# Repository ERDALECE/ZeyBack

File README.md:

# ZeyBack R2RDAC

High-performance DIY USB Audio / FPGA based R-2R DAC platform.

The STM32H750 MCU plays audio in 44.1 kHz - 768 kHz PCM and DSD64 - DSD512 DSD (DoP) formats. 

Optionally, a second USB audio input can be added by connecting an XMOS or AMANERO.

SPDIF audio input up to 192 kHz is possible via the CS8416 or directly through the FPGA input.

It has one coaxial and two optical inputs.

HDMI audio input is possible with the ADV7611.

Direct I2S signal pins are also provided. An external I2S signal can also be supplied as an input through these pins.

With the SI5340, the reclocking operation is performed within the FPGA.

Input selection via infrared remote control is possible using the RC5 code. Debugging can be done via a separate USB COM port. 
Status information (sample rate, bitrate, selected input, etc.) is output as SPI from the FPGA.
MCUs, displays, etc., can be connected to SPI pins to display information via a GUI.

Main PCB is 6 Layer, DSD PCB is 4 Layer. 

All tests have been completed and no serious bugs have been found. However, it is open to improvement.

This repository contains:
- STM32H750 USB Audio Class 2.0 (UAC2) firmware (PCM + DSD related work)
- FPGA logic used for audio data path / clocking / I2S/DSD processing
- Hardware design files (KiCad schematics/PCB, BOM, Gerbers)

## Repository structure

- `Firmware/Stm32/`  
  STM32H750 project (STM32CubeIDE). Includes STM32Cube/HAL and middleware components.

- `Firmware/Fpga/`  
  FPGA project files (Vivado project + sources).

- `Hardware/`  
  KiCad project files, BOM/CSV, and manufacturing outputs (Gerbers).
  
- `Pictures/` 
  Some testing and pcb pictures.

## Build / Tools

- STM32: STM32CubeIDE (or gcc-arm + Make/CMake if you prefer)
- FPGA: Xilinx Vivado
- Hardware: KiCad

## DSD Native / Volumio notes

Goal: DSD Native playback on Linux (Volumio / Raspberry Pi) with proper USB descriptors and, if required,
a targeted `snd-usb-audio` quirk limited to this device (VID+PID).

## Licensing (IMPORTANT)

This repository is **multi-licensed**:

- **Firmware** (our original code): **GPL-3.0-or-later**
- **Hardware design files** (KiCad schematics/PCB): **CERN-OHL-S-2.0**
- **Documentation** (if/when added under `docs/`): **CC BY-SA 4.0**
- **Third-party components** (e.g., STM32Cube/HAL, middleware): keep their **original licenses**
  as stated in file headers and vendor license texts.

See:
- `LICENSE` (GPLv3 for the main project codebase)
- `Firmware/LICENSE` (firmware scope)
- `Hardware/LICENSE` (hardware scope)
- `THIRD_PARTY_NOTICES.md`

## Status

Work in progress....
Hardware design files in this directory (KiCad schematics/PCB and related design sources)
are licensed under CERN-OHL-S-2.0 (Strongly Reciprocal).

Manufacturing outputs (Gerbers) are provided for convenience.

See THIRD_PARTY_NOTICES.md for any third-party footprints/symbols (if applicable).

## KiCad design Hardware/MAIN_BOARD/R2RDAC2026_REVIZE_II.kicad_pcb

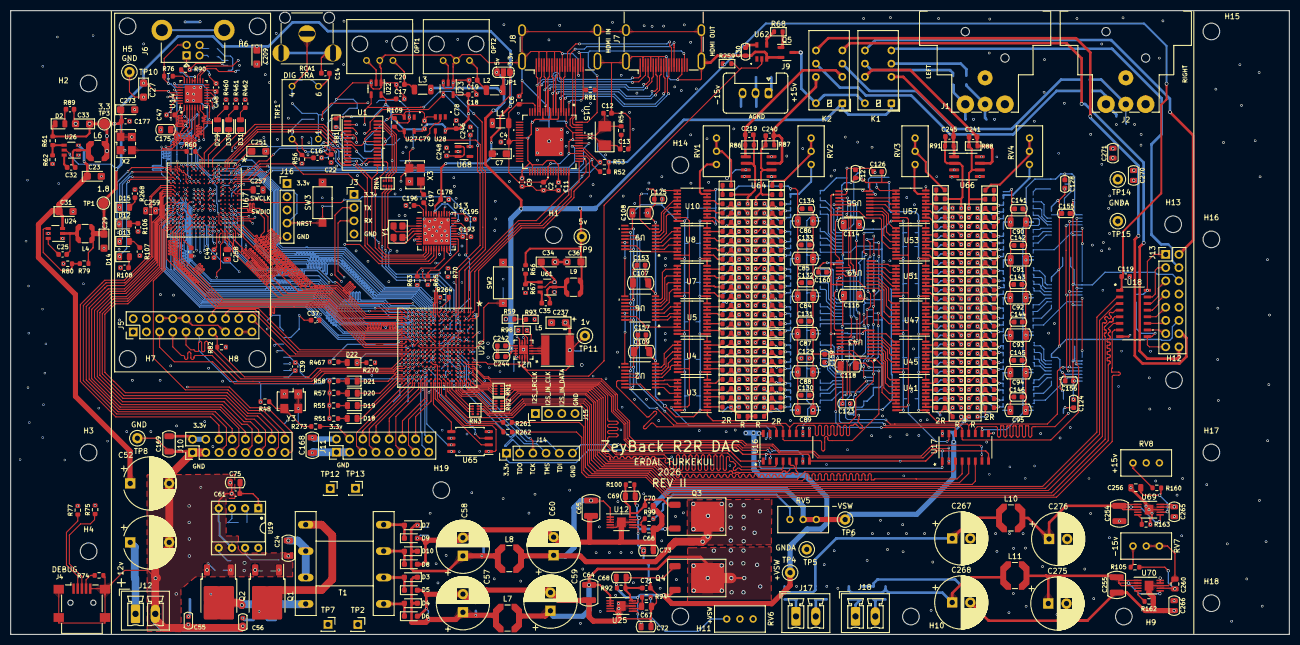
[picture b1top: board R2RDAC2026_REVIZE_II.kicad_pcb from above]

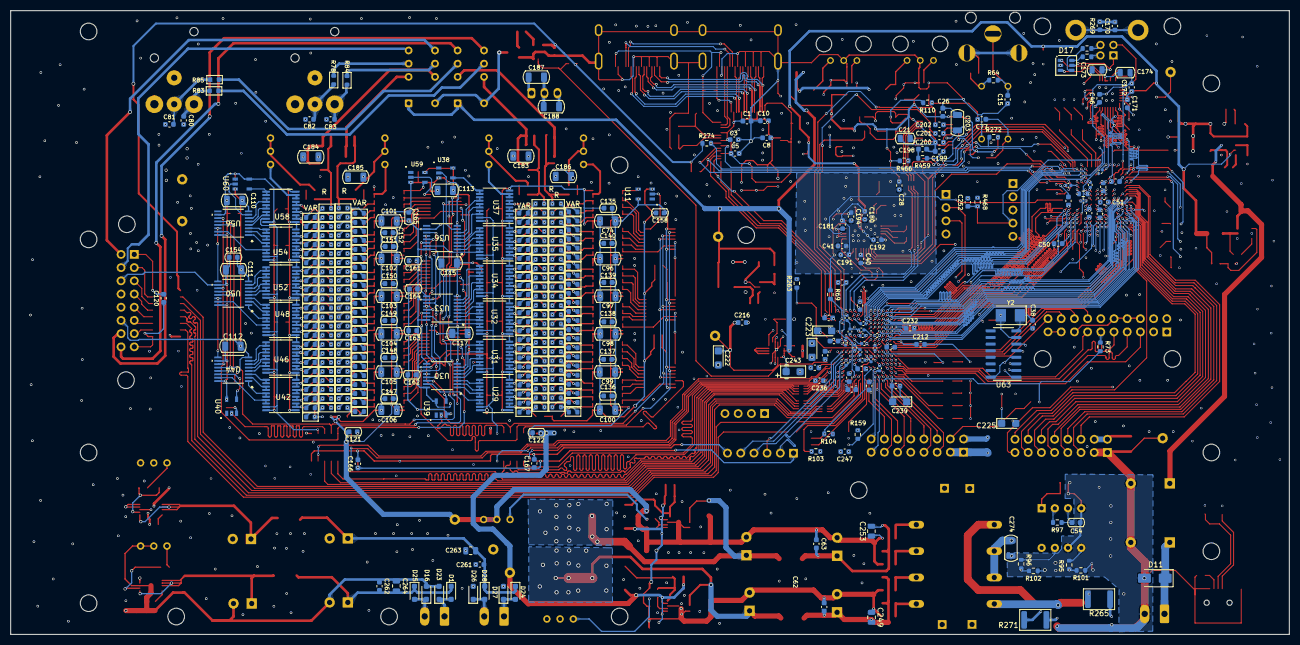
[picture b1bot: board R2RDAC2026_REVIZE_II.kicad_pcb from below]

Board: 6 copper layers, 246.0 x 120.0 mm, 940 parts (390 on the bottom side), 793 nets.

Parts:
C1, C2, C3, C4, C5, C6, C8, C9, C10, C11, C14, C15, C17, C18, C22, C26, C28, C30, C40, C41, C42, C43, C44, C46, C47, C48, C49, C50, C51, C78, C79, C119, C120, C121, C122, C123, C124, C125, C127, C128, C129, C130, C131, C132, C133, C134, C135, C136, C137, C139, C140, C141, C142, C143, C144, C145, C146, C147, C148, C149, C151, C152, C153, C154, C155, C156, C157, C158, C159, C160, C162, C163, C164, C165, C166, C167, C171, C172, C176, C177, C178, C180, C181, C191, C192, C193, C194, C195, C196, C197, C206, C221, C244, C250, C252: 100nf; C_0603_1608Metric
C7, C23, C27, C29, C33, C36, C209, C222, C223, C224, C225, C239, C251, C273: 10uf/6.3; CP_EIA-3216-18_Kemet-A
C12, C13: 22pf; C_0603_1608Metric
C16, C55, C56, C77: 10nf; C_0603_1608Metric
C19, C20: 1 uf; C_0603_1608Metric
C21: 1uf; C_0805_2012Metric
C24, C274: 10uF; C_1206_3216Metric
C25, C32, C35, C61, C62, C63, C179, C207, C212, C216, C226, C227, C229, C230, C231, C232, C233, C234, C235, C236, C238, C247, C261, C262: 100 nf; C_0603_1608Metric
C31, C34: 10uf/16v; CP_EIA-3216-18_Kemet-A
C37, C38: 22 pf; C_0603_1608Metric
C39, C200, C201, C202: 10 nf; C_0603_1608Metric
C45, C76, C189, C190, C204, C205, C208, C213, C214, C215, C217, C218, C220, C228, C272: 100 nf; C_0402_1005Metric
C52, C53: CP_Radial_D8.0mm_P2.50mm; CP_Radial_D10.0mm_P7.50mm
C54: 470pf; C_0603_1608Metric
C57, C58, C59, C60: 1000uf/10v; CP_Radial_D10.0mm_P3.50mm
C64, C65, C254, C255: 47uf/10v; C_1210_3225Metric
C66, C67, C256, C260: 4.7uf; C_0805_2012Metric
C68, C69, C72, C73, C265, C266, C270, C271: 10uf; C_0805_2012Metric
C70, C71, C246, C248: 4.7uf; C_0603_1608Metric
C74, C84, C85, C86, C87, C88, C89, C90, C91, C92, C93, C94, C95, C96, C97, C98, C99, C100, C101, C102, C103, C104, C105, C106, C107, C108, C109, C110, C111, C112, C113, C114, C115, C116, C117, C118, C168, C169, C183, C184, C185, C186, C187, C188, C203: 100uf; C_1206_3216Metric
C75: 10uF; C_0805_2012Metric
C80, C81, C82, C83, C219, C240, C241, C245: 100 pf; C_0603_1608Metric
C126, C138, C150, C161: 100uf; C_0603_1608Metric
C170, C199: 1 nf; C_0603_1608Metric
C173, C174, C175: 2.2uf; C_0805_2012Metric
C182, C210, C211, C269: 100nf; C_0402_1005Metric
C198: 22 nf; C_0603_1608Metric
C237: 47uf/6.3; CP_EIA-3216-18_Kemet-A
C242: 3.3nf; C_0603_1608Metric
C243: 4,7uF/16; CP_EIA-3216-18_Kemet-A
C249, C257, C258, C259, C263: 1 uf; C_0805_2012Metric
C253, C264: 1 uF; C_0805_2012Metric
C267, C268, C275, C276: 470uf/16v; CP_Radial_D10.0mm_P3.50mm
D1, D3, D4, D5, D6, D7, D8, D9, D10, D16, D23, D24, D25, D26, D27, D28: DSS20-0015B; D_SOD-323_HandSoldering
D2, D12, D13, D14, D15, D18, D19, D20, D21, D22, D29, D30, D31: RED; LED_0805_2012Metric
D11: DSS20-0015B; D_SMA
D17: USBLC6-2SC6; SOT-23-6
FB1: FerriteBead_Small; R_0603_1608Metric
H1, H2, H3, H4, H5, H6, H7, H8, H9, H10, H11, H12, H13, H14, H15, H16, H17, H18, H19: MountingHole; MountingHole_3.2mm_M3
J1, J2: NC3MBH-B; Jack_XLR_Neutrik_NC3MBH-B_Horizontal
J3: Conn_01x04; PinHeader_1x04_P2.54mm_Vertical
J4: USB_B_Micro; USB_Mini-B_Lumberg_2486_01_Horizontal
J5: XMOS; PinHeader_2x10_P2.54mm_Vertical
J6: USB_B; USB_B_Lumberg_2411_02_Horizontal
J7, J8: HDMI_A; HDMI_A_Molex_208658-1001_Horizontal
J9: Conn_01x03_Pin; Stocko_MKS_1653-6-0-303_1x3_P2.50mm_Vertical
J10, J11, J13: Conn_02x08_Odd_Even; PinHeader_2x08_P2.54mm_Vertical
J12, J17, J18: Conn_01x02; PhoenixContact_MCV_1,5_2-G-3.81_1x02_P3.81mm_Vertical
J14: Conn_01x06; PinHeader_1x06_P2.54mm_Vertical
J15: Conn_01x04_Pin; PinHeader_1x04_P2.54mm_Vertical
J16: Conn_01x05; PinHeader_1x05_P2.54mm_Vertical
JP1: Jumper_3_Open; SolderJumper-3_P1.3mm_Open_RoundedPad1.0x1.5mm_NumberLabels
K1, K2: EC2-5NU; Relay_DPDT_Kemet_EC2
L1: 10 uH; L_1206_3216Metric
L2, L3: 1 uH; L_1206_3216Metric
L4, L9: 2,2uH; L_Coilcraft_LPS3314
L5: 2.2uh; L_Taiyo-Yuden_NR-60xx
L6: 3,3uH; L_Coilcraft_LPS4018
L7, L8, L10, L11: 10uH; L_Coilcraft_LPS5030
OPT1, OPT2: TORX177
Q1, Q2: IRFR120N; TO-252-2
Q3, Q4: MJD44H11; TO-252-2
Q5: BC847; SOT-23-3
R1, R2, R3, R4, R5, R6, R7, R8, R16, R19, R21, R23, R25, R27, R29, R31, R33, R35, R37, R39, R41, R43, R45, R47, R49, R111, R112, R114, R116, R118, R120, R122, R124, R126, R128, R130, R132, R134, R136, R138, R140, R142, R144, R146, R148, R150, R152, R154, R156, R158, R164, R165, R166, R167, R170, R171, R174, R175, R178, R179, R182, R183, R186, R187, R190, R191, R194, R195, R198, R199, R202, R203, R206, R207, R210, R211, R214, R215, R218, R219, R222, R223, R226, R227, R230, R231, R234, R235, R238, R239, R242, R243, R246, R247, R250, R251, R254, R255, R258, R260: 2R; R_0603_1608Metric
R9, R10, R11, R12, R13, R14, R15, R17, R18, R20, R22, R24, R26, R28, R30, R32, R34, R36, R38, R40, R42, R44, R46, R113, R115, R117, R119, R121, R123, R125, R127, R129, R131, R133, R135, R137, R139, R141, R143, R145, R147, R149, R151, R153, R155, R157, R168, R169, R172, R173, R176, R177, R180, R181, R184, R185, R188, R189, R192, R193, R196, R197, R200, R201, R204, R205, R208, R209, R212, R213, R216, R217, R220, R221, R224, R225, R228, R229, R232, R233, R236, R237, R240, R241, R244, R245, R248, R249, R252, R253, R256, R257, R275, R276, R277, R278, R279, R280, R281, R282, R283, R284, R285, R286, R287, R288, R289, R290, R291, R292, R293, R294, R295, R296, R297, R298, R299, R300, R301, R302, R303, R304, R305, R306, R307, R308, R309, R310, R311, R312, R313, R314, R315, R316, R317, R318, R319, R320, R321, R322, R323, R324, R325, R326, R327, R328, R329, R330, R331, R332, R333, R334, R335, R336, R337, R338, R339, R340, R341, R342, R343, R344, R345, R346, R347, R348, R349, R350, R351, R352, R353, R354, R355, R356, R357, R358, R359, R360, R361, R362, R363, R364, R365, R366: R; R_0603_1608Metric
R48, R60, R73, R273: 33; R_0603_1608Metric
R50, R161, R266, R267, R367, R368, R369, R370, R371, R372, R373, R374, R375, R376, R377, R378, R379, R380, R381, R382, R383, R384, R385, R386, R387, R388, R389, R390, R391, R392, R393, R394, R395, R396, R397, R398, R399, R400, R401, R402, R403, R404, R405, R406, R407, R408, R409, R410, R411, R412, R413, R414, R415, R416, R417, R418, R419, R420, R421, R422, R423, R424, R425, R426, R427, R428, R429, R430, R431, R432, R433, R434, R435, R436, R437, R438, R439, R440, R441, R442, R443, R444, R445, R446, R447, R448, R449, R450, R451, R452, R453, R454, R455, R456, R457, R458: VAR; R_0603_1608Metric
R51, R55, R57, R58, R68, R162, R163, R263, R270, R467: 1k; R_0603_1608Metric
R52, R53, R81, R82, R272, R466: 4,7k; R_0603_1608Metric
R54: 390k; R_0603_1608Metric
R56, R64: 75; R_0603_1608Metric
R59: 51k; R_0603_1608Metric
R61: 22.1k; R_0603_1608Metric
R62, R98: 100k; R_0603_1608Metric
R63, R65, R69, R70, R71, R72, R261, R262: 22; R_0603_1608Metric
R66: 54.9k; R_0603_1608Metric
R67, R80, R90, R92, R100, R109, R259, R274, R468, R470: 10k; R_0603_1608Metric
R74: 1,5k; R_0603_1608Metric
R75, R77: 27; R_0603_1608Metric
R76: 8.06k; R_0603_1608Metric
R78, R83, R84, R85, R86, R87, R88, R91, R110: 100; R_0603_1608Metric
R79: 13,7k; R_0603_1608Metric
R89, R106, R107, R108, R268, R460, R461, R462: 1k; C_0603_1608Metric
R93: 200k; R_0603_1608Metric
R94, R99, R105, R160: 31k; R_0603_1608Metric
R95, R96: 10; R_0603_1608Metric
R97: 15k; R_0603_1608Metric
R101, R102: 47k; R_0603_1608Metric
R103, R104, R159, R264: 4.7k; R_0603_1608Metric
R265, R271: 10; R_1812_4532Metric
R269: 1m; C_0603_1608Metric
R459: 3k; R_0603_1608Metric
RCA1: RCA
RN1, RN2, RN3, RN4: R_4x0402_Convex; R_Array_Convex_4x0402
RV1, RV2, RV3, RV4: 50; Potentiometer_Bourns_3296W_Vertical
RV5, RV6, RV7, RV8: 2.2k; Potentiometer_Bourns_3296W_Vertical
SW2, SW3: SW_Push; SW_SPST_CK_RS282G05A3
T1: Transformer_1P_2S; EE2006
TP1, TP3: TestPoint; TestPoint_Pad_D2.0mm
TP2, TP7, TP12, TP13: TestPoint; PinSocket_1x01_P2.54mm_Vertical
TP4, TP5, TP6, TP8, TP9, TP10, TP14, TP15: TestPoint; TestPoint_Loop_D2.50mm_Drill1.0mm
TP11: 1v; TestPoint_Loop_D2.50mm_Drill1.0mm
TRF1: DIGITALTRAFO
U1: CS8416-xZZ; TSSOP-28_4.4x9.7mm_P0.65mm
U2, U6, U9, U30, U33, U36, U43, U44, U49, U50, U55, U56: 74LS595; TSSOP16_SOT403-1_NXP_NEX
U3, U4, U5, U7, U8, U10, U29, U31, U32, U34, U35, U37, U41, U42, U45, U46, U47, U48, U51, U52, U53, U54, U57, U58: SN74LVC245AN; TSSOP-20_4.4x6.5mm_P0.65mm
U11, U27, U28, U38, U39, U40, U59, U60, U62: SN74LVC1G04DBVR; SOT-753
U12, U25, U69, U70: LT3042xMSE; MSOP-10-1EP_3x3mm_P0.5mm_EP1.68x1.88mm
U13: Si5342A-D; QFN-44-1EP_7x7mm_P0.5mm_EP5.2x5.2mm
U14: USB3320C-EZK; QFN32_5X5MC_MCH
U15: ADV7611BSWZ; SW_64_2_ADI
U16, U17, U18: SI8660BC-B-IS1R; SOIC16_SI823_SKY
U19: IR2153; DIP-8_W7.62mm_Socket
U20: XC7A100T-CSG324; BGA-324_15.0x15.0mm_Layout18x18_P0.8mm_Ball0.45mm_Pad0.4mm_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
U21: TPS62130RGTT; TPS62130
U22, U23: SN74LVC1G125DBVR; SOT-23-5
U24, U26, U61: TPS562201DDCR; DDC0006A_N
U63: CH340G; SOIC-16_3.9x9.9mm_P1.27mm
U64, U66: OPA2134UA; SOIC-8_3.9x4.9mm_P1.27mm
U65: W25Q128JVS; SOIC-8_5.23x5.23mm_P1.27mm
U67: STM32H750XBHx; TFBGA-265_14x14mm_Layout17x17_P0.8mm
U68: AP2127K-1.8; SOT-23-5
X1: 28.63636 mhz; Crystal_SMD_5032-2Pin_5.0x3.2mm
X2, X3: 24.576 mhz; Oscillator_SMD_SeikoEpson_SG8002LB-4Pin_5.0x3.2mm
Y1: Crystal_GND24; Crystal_SMD_3225-4Pin_3.2x2.5mm
Y2: 12 Mhz; Crystal_SMD_5032-2Pin_5.0x3.2mm
Y3: 50mhz; Oscillator_SMD_EuroQuartz_XO53-4Pin_5.0x3.2mm_HandSoldering

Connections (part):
1.8V_ENB: R98.2, U21.4 (PG), U24.5 (EN)
1.8v ADV: C246.1, L1.1 (+), U68.5 (VOUT)
24Mhz_ULPI: U14.26 (REFCLK), U67.E15 (PA8)
+1V0: C76.1, C190.1, C205.1, C213.1, C214.1, C215.1, C216.1, C217.1, C218.1, C220.1, C222.1, C223.1, C237.1, L5.1 (+), R59.1, TP11.1, U20.F8 (VCCINT), U20.F10 (VCCBRAM), U20.G7 (VCCINT), U20.G9 (VCCINT), U20.G11 (VCCBRAM), U20.H8 (VCCINT), U20.J7 (VCCINT), U20.J11 (VCCINT), U20.K8 (VCCINT), U20.L7 (VCCINT), U20.L11 (VCCINT), U20.M8 (VCCINT), U20.M10 (VCCINT), U20.N7 (VCCINT), U20.N9 (VCCINT), U20.N11 (VCCINT), U21.14 (VOS)
+1V8: C27.1, C29.1, C45.1, C171.1, C172.1, C178.1, C179.1, C180.1, C181.1, C191.1, C204.1, C207.1, C208.1, C209.1, L4.2, R79.1, TP1.1, U13.21 (VDD), U13.32 (VDD), U13.39 (VDD), U13.40 (VDD), U14.28 (VDD18), U14.30 (VDD18), U20.E8 (VCCBATT_0), U20.F12 (VCCAUX), U20.H10 (VCCADC_0), U20.H12 (VCCAUX), U20.K12 (VCCAUX), U20.M12 (VCCAUX), U26.5 (EN)
+3.3V: C8.1, C9.1, C10.1, C11.1, C17.1, C18.1, C21.2, C22.2, C26.2, C28.1, C30.1, C33.1, C39.1, C40.1, C41.1, C42.1, C43.1, C44.1, C46.1, C47.1, C48.1, C49.1, C50.1, C51.1, C78.1, C79.1, C119.1, C166.1, C167.1, C168.1, C169.1, C174.1, C175.2, C176.1, C177.1, C182.1, C189.1, C192.1, C193.1, C194.1, C195.1, C206.1, C210.1, C211.1, C212.1, C221.1, C224.1, C225.1, C226.1, C227.1, C228.1, C229.1, C230.1, C231.1, C232.1, C233.1, C234.1, C235.1, C236.1, C238.1, C239.1, C247.1, C248.1, C250.1, C251.1, C269.1, C272.1, C273.1, D2.1, FB1.1, J3.1, J10.2, J10.4, J11.2, J14.1, J16.1, JP1.3 (B), L6.2, R52.1, R53.2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
+3.3VP: J5.17, J5.19
+5V: C36.1, C243.1, C244.1, JP1.1 (A), K1.1, K2.1, L9.2, R66.1, R98.1, TP9.1, U21.10 (AVIN), U21.11 (PVIN), U21.12 (PVIN), U21.13 (EN)
+12V: C23.1, C24.1, C31.1, C34.1, C52.1, C53.1, C61.2, C75.2, C274.1, D11.1 (K), J12.1, T1.2, T1.3, U19.1 (VCC), U19.8 (VB), U24.3 (VIN), U26.3 (VIN), U61.3 (VIN), U61.5 (EN)
+15V: C183.1, C184.1, C187.1, C265.1, C270.1, J9.1, U64.8 (V+), U66.8 (V+), U69.9 (OUTS), U69.10 (OUT)
+VSW: C68.2, C72.1, C74.1, C84.1, C85.1, C86.1, C87.1, C88.1, C89.1, C90.1, C91.1, C92.1, C93.1, C94.1, C95.1, C96.1, C97.1, C98.1, C99.1, C100.1, C101.1, C102.1, C103.1, C104.1, C105.1, C106.1, C107.1, C108.1, C109.1, C110.1, C111.1, C112.1, C113.1, C114.1, C115.1, C116.1, C117.1, C118.1, C121.1, C122.1, C123.1, C124.1, C125.1, C126.1, C127.1, C128.1, C129.1, C130.1, C131.1, C132.1, C133.1, C134.1, C135.1, C136.1, C137.1, C138.1, C139.1, C140.1, C141.1, C142.1, C143.1, C144.1, C145.1, C146.1, C147.1, C148.1, C149.1, C150.1, C151.1, C152.1, C153.1, C154.1, C155.1, C156.1, C157.1, C158.1, C159.1, C160.1, C161.1, C162.1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
-15V: C185.1, C186.1, C188.1, C255.1, C260.2, C262.1, C264.1, C266.2, C268.2, C271.1, C275.2, D16.2 (A), D23.2 (A), J9.3, R162.1, RV7.1, RV7.2, U64.4 (V-), U66.4 (V-), U70.8 (GND), U70.11 (GND)
-VSW: C58.2, C60.2, C63.1, C65.1, C66.2, C70.2, C73.2, C74.2, C84.2, C85.2, C86.2, C87.2, C88.2, C89.2, C90.2, C91.2, C92.2, C93.2, C94.2, C95.2, C96.2, C97.2, C98.2, C99.2, C100.2, C101.2, C102.2, C103.2, C104.2, C105.2, C106.2, C107.2, C108.2, C109.2, C110.2, C111.2, C112.2, C113.2, C114.2, C115.2, C116.2, C117.2, C118.2, C121.2, C122.2, C123.2, C124.2, C125.2, C126.2, C127.2, C128.2, C129.2, C130.2, C131.2, C132.2, C133.2, C134.2, C135.2, C136.2, C137.2, C138.2, C139.2, C140.2, C141.2, C142.2, C143.2, C144.2, C145.2, C146.2, C147.2, C148.2, C149.2, C150.2, C151.2, C152.2, C153.2, C154.2, C155.2, C156.2, C157.2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
A0: U20.M2 (IO_L4N_T0_34), U67.G4 (PF0)
A1: U20.K3 (IO_L2P_T0_34), U67.G3 (PF1)
BCLK_L: U2.11 (SRCLK), U6.11 (SRCLK), U9.11 (SRCLK), U16.13 (B3), U30.11 (SRCLK), U33.11 (SRCLK), U36.11 (SRCLK)
BCLK_L_F: RN1.3 (R3.1), U16.4 (A3)
BCLK_R: U17.13 (B3), U43.11 (SRCLK), U44.11 (SRCLK), U49.11 (SRCLK), U50.11 (SRCLK), U55.11 (SRCLK), U56.11 (SRCLK)
BCLK_R_F: RN2.3 (R3.1), U17.4 (A3)
CCLK: U20.E9 (CCLK_0), U65.6 (CLK)
CEC: J7.13 (CEC), J8.13 (CEC)
COAX: C16.2, U1.4 (RXP0)
COAX_FPGA_IN: C77.2, R110.1
COAX_FPGA_OUT: U20.E2 (IO_L14P_T2_SRCC_35), U28.4 (Y)
CSB: U1.14 (AD0/~CS/NV/RERR), U67.D2 (PE4)
CSB_SI: U13.16 (A0/~CS), U67.A3 (PI5)
CSO: R103.2, U20.L13 (IO_L6P_T0_FCS_B_14), U65.1 (~CS)
D0: U20.K17 (IO_L1P_T0_D00_MOSI_14), U65.5 (DI(IO0))
D1: U20.K18 (IO_L1N_T0_D01_DIN_14), U65.2 (DO(IO1))
D2: R104.2, U20.L14 (IO_L2P_T0_D02_14), U65.3 (IO2)
D3: R159.2, U20.M14 (IO_L2N_T0_D03_14), U65.7 (IO3)
D+: D17.3 (L2), U14.18 (DP)
D-: D17.1 (L1), U14.19 (DM)
DATA_N_L: U16.11 (B5), U39.2 (A)
DATA_N_L_F: RN1.1 (R1.1), U16.6 (A5)
DATA_N_R: U17.11 (B5), U40.2 (A)
DATA_N_R_F: RN2.1 (R1.1), U17.6 (A5)
DATA_P_L: U2.14 (SER), U16.14 (B2)
DATA_P_L_F: RN1.4 (R4.1), U16.3 (A2)
DATA_P_R: U17.14 (B2), U43.14 (SER)
DATA_P_R_F: RN2.4 (R4.1), U17.3 (A2)
DIR: U14.31 (DIR), U67.F4 (PI11)
DS0: U20.U7 (IO_L22P_T3_34), U67.P16 (PD14)
DS1: U20.P3 (IO_L14N_T2_SRCC_34), U67.P15 (PD15)
DS2: U20.R5 (IO_L19N_T3_VREF_34), U67.D13 (PD0)
DS3: U20.N2 (IO_L3P_T0_DQS_34), U67.E12 (PD1)
DS4: U20.R2 (IO_L15N_T2_DQS_34), U67.U9 (PE7)
DS5: U20.P2 (IO_L15P_T2_DQS_34), U67.T9 (PE8)
DS6: U20.T1 (IO_L17N_T2_34), U67.P9 (PE9)
DS7: U20.R1 (IO_L17P_T2_34), U67.N9 (PE10)
DS8: U20.U1 (IO_L7P_T1_34), U67.P10 (PE11)
DS9: U20.V1 (IO_L7N_T1_34), U67.R10 (PE12)
DS10: U20.R7 (IO_L23P_T3_34), U67.T10 (PE13)
DS11: U20.R8 (IO_L24P_T3_34), U67.U10 (PE14)
DS12: U20.T3 (IO_L11N_T1_SRCC_34), U67.R11 (PE15)
DS13: U20.U9 (IO_L21P_T3_DQS_34), U67.U16 (PD8)
DS14: U20.U8 (IO_25_34), U67.T17 (PD9)
DS15: U20.V9 (IO_L21N_T3_DQS_34), U67.T16 (PD10)
DS16: U20.N6 (IO_L18N_T2_34), U67.T13 (PH8)
DS17: U20.R6 (IO_L19P_T3_34), U67.R13 (PH9)
DS18: U20.P4 (IO_L14P_T2_SRCC_34), U67.P13 (PH10)
DS19: U20.R3 (IO_L11P_T1_SRCC_34), U67.P14 (PH11)
DS20: U20.T6 (IO_L23N_T3_34), U67.R14 (PH12)
DS21: U20.V6 (IO_L20N_T3_34), U67.D16 (PH13)
DS22: U20.U6 (IO_L22N_T3_34), U67.B17 (PH14)
DS23: U20.V5 (IO_L10P_T1_34), U67.B16 (PH15)
DS24: U20.V4 (IO_L10N_T1_34), U67.A16 (PI0)
DS25: U20.U3 (IO_L8N_T1_34), U67.A15 (PI1)
DS26: U20.U4 (IO_L8P_T1_34), U67.B15 (PI2)
DS27: U20.N4 (IO_L16N_T2_34), U67.C14 (PI3)
DS28: U20.M6 (IO_L18P_T2_34), U67.A2 (PI6)
DS29: U20.L3 (IO_L2N_T0_34), U67.B3 (PI7)
DS30: U20.L4 (IO_L5N_T0_34), U67.E2 (PI9)
DS31: U20.L1 (IO_L1P_T0_34), U67.F3 (PI10)
DSD_A: RN3.3 (R3.1), U18.3 (A2)
DSD_A_N: R261.2, U18.6 (A5)
DSD_B: RN3.2 (R2.1), U18.4 (A3)
DSD_B_N: R262.2, U18.7 (A6)
DSD_CLK: RN3.4 (R4.1), U18.2 (A1)
DSD_EN: U18.5 (A4), U20.H17 (IO_L18P_T2_A24_15)
DSD_EN_RL: R259.1, U20.A13 (IO_L9P_T1_DQS_AD3P_15), U62.2 (A)
DSD_ON: J5.13, R82.2, U20.V12 (IO_L20N_T3_A07_D23_14)
F0: J5.14, U20.V10 (IO_L21P_T3_DQS_14)
F1: J5.16, U20.T10 (IO_L24N_T3_A00_D16_14)
F2: J5.18, U20.V11 (IO_L21N_T3_DQS_A06_D22_14)
F3: J5.20, U20.U11 (IO_L19N_T3_A09_D25_VREF_14)
GND: C1.2, C2.2, C3.2, C4.2, C5.2, C6.2, C7.2, C8.2, C9.2, C10.2, C11.2, C12.2, C13.2, C15.1, C17.2, C18.2, C19.1, C20.1, C21.1, C22.1, C23.2, C24.2, C26.1, C27.2, C28.2, C29.2, C30.2, C31.2, C33.2, C34.2, C36.2, C37.1, C38.2, C39.2, C40.2, C41.2, C42.2, C43.2, C44.2, C45.2, C46.2, C47.2, C48.2, C49.2, C50.2, C51.2, C52.2, C53.2, C54.2, C55.2, C56.2, C61.1, C75.1, C76.2, C78.2, C79.2, C119.2, C166.2, C167.2, C168.2, C169.2, C170.2, C171.2, C172.2, C173.2, C174.2, C175.1, C176.2, C177.2, C178.2, C179.2, C180.2, C181.2, C182.2, C189.2, C190.2, C191.2, C192.2, C193.2, C194.2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
GNDA: C57.2, C59.2, C62.1, C64.1, C67.2, C69.2, C71.2, C72.2, C73.1, C80.2, C81.1, C82.1, C83.2, C183.2, C184.2, C185.2, C186.2, C187.2, C188.2, C249.1, C254.1, C256.2, C261.1, C263.1, C265.2, C266.1, C267.2, C270.2, C271.2, C276.2, D5.2 (A), D6.2 (A), D26.2 (A), D27.2 (A), J1.1, J1.G, J2.1, J2.G, J9.2, J13.10, Q3.3 (E), R100.1, R163.1, RV6.1, RV6.2, RV8.1, RV8.2, TP5.1, TP14.1, TP15.1, U12.6 (PGFB), U12.9 (OUTS), U25.5 (ILIM), U25.8 (GND), U25.11 (GND), U64.3 (+), U64.5 (+), U66.3 (+), U66.5 (+), U69.8 (GND), U69.11 (GND), U70.9 (OUTS), U70.10 (OUT)
HDMI_I2S_BCLK: U15.49 (SCLK/INT2), U20.A1 (IO_L9N_T1_DQS_AD7N_35)
HDMI_I2S_DATA: U15.48 (AP), U20.B2 (IO_L10N_T1_AD15N_35)
HDMI_I2S_LRCLK: U15.50 (LRCLK), U20.B1 (IO_L9P_T1_DQS_AD7P_35)
HDMI_INDSCL: J8.15 (SCL), U15.62 (DDCA_SCL)
HDMI_INDSDA: J8.16 (SDA), U15.63 (DDCA_SDA)
HDMI_IN_5v: J7.18 (+5V), J8.18 (+5V), R81.1, U15.64 (RXA_5V)
HDMI_IN_INT1: U15.55 (INT1), U67.B4 (PE1)
HDMI_IN_MCLK: U15.51 (MCLK/INT2), U20.B3 (IO_L10P_T1_AD15P_35)
HDMI_IN_RESET: R274.2, U15.56 (*RESET), U67.A4 (PI4)
HDMI_IN_SCL: R52.2, U15.53 (SCL), U67.B5 (PB6)
HDMI_IN_SDA: R53.1, U15.54 (SDA), U67.C5 (PB7)
HPD: J8.19 (HPD), R81.2, U15.1 (HPA_A/INT2)
I2S_IN_CLK: J15.2, U20.D15 (IO_L12P_T1_MRCC_15)
I2S_IN_DATA: J15.3, U20.E16 (IO_L11N_T1_SRCC_15)
I2S_IN_LRCLK: J15.1, U20.E15 (IO_L11P_T1_SRCC_15)
IO0: J11.5, U20.U18 (IO_L17N_T2_A13_D29_14)
IO1: J11.6, U20.T18 (IO_L7N_T1_D10_14)
IO2: J11.7, U20.R17 (IO_L12N_T1_MRCC_14)
IO3: J11.8, U20.R18 (IO_L7P_T1_D09_14)
IO4: J11.9, U20.R16 (IO_L15P_T2_DQS_RDWR_B_14)
IO5: J11.10, U20.P18 (IO_L9N_T1_DQS_D13_14)
IO6: J11.11, U20.N17 (IO_L9P_T1_DQS_14)
IO7: J11.12, U20.M17 (IO_L10N_T1_D15_14)
IO8: J11.13, U20.M18 (IO_L4N_T0_D05_14)
IO9: J11.14, U20.L18 (IO_L4P_T0_D04_14)
IO10: J11.15, U20.N16 (IO_L11N_T1_SRCC_14)
IO11: J11.16, U20.M16 (IO_L10P_T1_D14_14)
IO12: J11.4, R273.2
IR: J10.12, U67.R9 (PF15)
LCLK: U2.12 (RCLK), U6.12 (RCLK), U9.12 (RCLK), U16.12 (B4), U30.12 (RCLK), U33.12 (RCLK), U36.12 (RCLK)
LCLK_F: RN1.2 (R2.1), U16.5 (A4)
LED1: D15.1, U67.U3 (PA4)
LED2: D12.1, U67.R3 (PA6)
LED3: D13.1, U67.T4 (PC4)
LED4: D14.1, U67.U4 (PC5)
LED5: D29.1, U67.J1 (PH1)
LED6: D30.1, U67.H1 (PI12)
LED7: D31.1, U67.G1 (PF2)
LEDF1: D21.1, U20.V16 (IO_L16N_T2_A15_D31_14)
LEDF2: D20.1, U20.U16 (IO_L18P_T2_A12_D28_14)
LEDF3: D19.1, U20.V17 (IO_L18N_T2_A11_D27_14)
LEDF4: D18.1, U20.U17 (IO_L17P_T2_A14_D30_14)
LEFT+: C219.2, R46.2, R47.2, R86.1, R297.2, U64.2 (-)
LEFT-: C240.2, R87.1, R157.2, R158.2, R320.2, U64.6 (-)
LEFT_OUT+: C240.1, K2.10, R87.2, U64.7
LEFT_OUT-: C219.1, K2.3, R86.2, U64.1
MCU_CLK: R60.2, X2.3 (OUT)
NE1: U20.N1 (IO_L3N_T0_DQS_34), U67.C11 (PD7)
NOE: U20.V2 (IO_L9N_T1_DQS_34), U67.A12 (PD4)
NRST: C252.1, J16.4, R468.2, SW3.1, U67.K1 (NRST)
NWAIT: U20.M1 (IO_L1N_T0_34), U67.B11 (PD6)
NWE: U20.U2 (IO_L9P_T1_DQS_34), U67.A11 (PD5)
NXT: U14.2 (NXT), U67.M4 (PC3)
unnamed: C14.1, RCA1.BREAK, RCA1.SPRING
unnamed: C14.2, R64.1, TRF1.6
unnamed: C15.2, R64.2, RCA1.BARREL, TRF1.4
unnamed: C16.1, C77.1, R56.1, TRF1.3
unnamed: C55.1, R265.1
unnamed: C56.1, R271.1
unnamed: C80.1, J2.2, R83.1
unnamed: C81.2, J2.3, R85.1
unnamed: C82.2, J1.3, R78.1
unnamed: C83.1, J1.2, R84.1
unnamed: C198.2, R459.2
unnamed: C257.1, U67.A7 (VCAP)
unnamed: C258.1, U67.D17 (VCAP)
unnamed: C259.1, U67.U11 (VCAP)
unnamed: D1.2 (A), D23.1 (K), J18.1, TP13.1
unnamed: C262.2, C264.2, C268.1, D1.1 (K), D25.1 (K), L11.1
unnamed: D2.2, R89.1
unnamed: D3.2 (A), D5.1 (K), T1.7
unnamed: C57.1, C62.2, C249.2, D3.1 (K), D4.1 (K), L7.1
unnamed: D4.2 (A), D6.1 (K), T1.8
unnamed: D7.2 (A), D9.1 (K), T1.5
unnamed: D8.1 (K), D10.2 (A), T1.6
unnamed: C58.1, C63.2, C253.2, D7.1 (K), D10.1 (K), L8.1
unnamed: D12.2, R106.1
unnamed: D13.2, R107.1
unnamed: D14.2, R108.1
unnamed: D15.2, R268.1
unnamed: D16.1 (K), D25.2 (A), J18.2, TP12.1
unnamed: D17.6 (L1), R71.1
unnamed: D17.4 (L2), R72.1
unnamed: C173.1, D17.5 (VP), J6.1 (VBUS), R90.2
unnamed: D18.2, R51.1
unnamed: D19.2, R55.1
unnamed: D20.2, R57.1
unnamed: D21.2, R58.1
unnamed: D22.2, R467.1
unnamed: D24.2 (A), D27.1 (K), J17.1, TP2.1
unnamed: C261.2, C263.2, C267.1, D24.1 (K), D28.1 (K), L10.1
unnamed: D26.1 (K), D28.2 (A), J17.2, TP7.1
unnamed: D29.2, R460.1
unnamed: D30.2, R461.1
unnamed: D31.2, R462.1
unnamed: J4.3 (D+), R75.1
unnamed: J4.2 (D-), R77.1
unnamed: J4.4 (ID), R74.2
unnamed: J5.11, R73.1
unnamed: J6.3 (D+), R72.2
unnamed: J6.2 (D-), R71.2
unnamed: C170.1, J6.5 (Shield), R269.1
unnamed: C120.2, J13.1, U18.16 (VDD2)
unnamed: J13.2, K1.8
unnamed: J13.3, U18.15 (B1)
unnamed: J13.4, K1.5
unnamed: J13.5, U18.14 (B2)
unnamed: J13.7, U18.13 (B3)
unnamed: J13.9, U18.12 (B4)
unnamed: J13.11, U18.11 (B5)
unnamed: J13.13, U18.10 (B6)
unnamed: J13.14, K2.8
unnamed: C120.1, J13.15, U18.9 (GND2)
unnamed: J13.16, K2.5
unnamed: JP1.2 (C), L2.2 (-), L3.2 (-)
unnamed: K1.4, R78.2
unnamed: K1.9, R84.2
unnamed: K2.4, R85.2
unnamed: K2.9, R83.2
unnamed: C1.1, C2.1, C3.1, C4.1, C5.1, C6.1, C7.1, L1.2 (-), U15.2 (CVDD), U15.14 (CVDD), U15.24 (DVDD), U15.40 (DVDD), U15.52 (DVDD), U15.57 (PVDD), U15.60 (DVDD)
unnamed: C19.2, L2.1 (+), OPT2.3 (VCC)
unnamed: C20.2, L3.1 (+), OPT1.3 (VCC)
unnamed: L5.2 (-), U21.1 (SW), U21.2 (SW), U21.3 (SW)
unnamed: OPT1.1 (OUT), U22.2 (A)
unnamed: OPT2.1 (OUT), U23.2 (A)
unnamed: Q1.2 (D), R271.2, T1.1
unnamed: Q1.1 (G), R96.2, R102.1
unnamed: Q2.2 (D), R265.2, T1.4
unnamed: Q2.1 (G), R95.2, R101.2
unnamed: C69.1, C70.1, Q3.1 (B), R100.2, U12.10 (OUT)
unnamed: C60.1, C65.2, L8.2, Q3.2 (C), U12.1 (IN), U12.2 (IN), U12.3 (EN/UV)
unnamed: C68.1, C71.1, Q4.1 (B), R92.2, U25.10 (OUT)
unnamed: C59.1, C64.2, L7.2, Q4.2 (C), U25.1 (IN), U25.2 (IN), U25.3 (EN/UV)
unnamed: Q5.1 (B), R68.2
unnamed: K1.12, K2.12, Q5.3 (C)
unnamed: R1.2, R49.1, R367.1
unnamed: R2.2, R9.2, R275.2, R368.1
unnamed: R10.1, R280.1, R372.2
unnamed: R7.2, R10.2, R280.2, R373.1
unnamed: R11.1, R276.1, R368.2
unnamed: R3.2, R11.2, R276.2, R369.1
unnamed: R12.1, R281.1, R373.2
unnamed: R8.2, R12.2, R281.2, R374.1
unnamed: R13.1, R277.1, R369.2
unnamed: R4.2, R13.2, R277.2, R370.1
unnamed: R14.1, R282.1, R374.2
unnamed: R14.2, R16.2, R282.2, R375.1
unnamed: R15.1, R278.1, R370.2
unnamed: R5.2, R15.2, R278.2, R371.1
unnamed: R17.1, R279.1, R371.2
unnamed: R6.2, R17.2, R279.2, R372.1
unnamed: R18.1, R283.1, R375.2
unnamed: R18.2, R19.2, R283.2, R376.1
unnamed: R20.1, R284.1, R376.2
unnamed: R20.2, R21.2, R284.2, R377.1
unnamed: R22.1, R285.1, R377.2
unnamed: R22.2, R23.2, R285.2, R378.1
unnamed: R24.1, R286.1, R378.2
unnamed: R24.2, R25.2, R286.2, R379.1
unnamed: R26.1, R287.1, R379.2
unnamed: R26.2, R27.2, R287.2, R380.1
unnamed: R28.1, R288.1, R380.2
unnamed: R28.2, R29.2, R288.2, R381.1
unnamed: R47.1, R50.2
unnamed: R50.1, RV1.2, RV1.3
unnamed: R94.1, RV6.3
unnamed: R99.1, RV5.3
unnamed: R105.1, RV7.3
unnamed: R111.2, R112.1, R390.2
unnamed: R113.1, R298.1, R390.1
unnamed: R113.2, R114.2, R298.2, R391.2
unnamed: R115.1, R299.1, R391.1
unnamed: R115.2, R116.2, R299.2, R392.1
unnamed: R117.1, R300.1, R392.2
unnamed: R117.2, R118.2, R300.2, R393.1
unnamed: R119.1, R301.1, R393.2
unnamed: R119.2, R120.2, R301.2, R394.1
unnamed: R121.1, R302.1, R394.2
unnamed: R121.2, R122.2, R302.2, R395.1
unnamed: R123.1, R303.1, R395.2
unnamed: R123.2, R124.2, R303.2, R396.1
unnamed: R125.1, R304.1, R396.2
unnamed: R125.2, R126.2, R304.2, R397.1
unnamed: R127.1, R305.1, R397.2
unnamed: R127.2, R128.2, R305.2, R398.1
unnamed: R129.1, R306.1, R398.2
unnamed: R129.2, R130.2, R306.2, R399.1
unnamed: R131.1, R307.1, R399.2
unnamed: R131.2, R132.2, R307.2, R400.1
unnamed: R133.1, R308.1, R400.2
unnamed: R133.2, R134.2, R308.2, R401.1
unnamed: R135.1, R309.1, R401.2
unnamed: R135.2, R136.2, R309.2, R402.1
unnamed: R137.1, R310.1, R402.2
unnamed: R137.2, R138.2, R310.2, R403.1
unnamed: R139.1, R311.1, R403.2
unnamed: R139.2, R140.2, R311.2, R404.1
unnamed: R141.1, R312.1, R404.2
unnamed: R141.2, R142.2, R312.2, R405.1
unnamed: R143.1, R313.1, R405.2
unnamed: R143.2, R144.2, R313.2, R406.1
unnamed: R145.1, R314.1, R406.2
unnamed: R145.2, R146.2, R314.2, R407.1
unnamed: R147.1, R315.1, R407.2
unnamed: R147.2, R148.2, R315.2, R408.1
unnamed: R149.1, R316.1, R408.2
unnamed: R149.2, R150.2, R316.2, R409.1
unnamed: R151.1, R317.1, R409.2
unnamed: R151.2, R152.2, R317.2, R410.1
unnamed: R153.1, R318.1, R410.2
unnamed: R153.2, R154.2, R318.2, R411.1
unnamed: R155.1, R319.1, R411.2
unnamed: R155.2, R156.2, R319.2, R412.1
unnamed: R157.1, R320.1, R412.2
unnamed: R158.1, R161.2
unnamed: R160.1, RV8.3
unnamed: R161.1, RV2.2, RV2.3
unnamed: R164.2, R165.1, R413.2
unnamed: R166.2, R167.1, R436.2
unnamed: R168.1, R321.1, R413.1
unnamed: R168.2, R170.2, R321.2, R414.1
unnamed: R169.1, R344.1, R436.1
unnamed: R169.2, R171.2, R344.2, R437.1
unnamed: R172.1, R322.1, R414.2
unnamed: R172.2, R174.2, R322.2, R415.1
unnamed: R173.1, R345.1, R437.2
unnamed: R173.2, R175.2, R345.2, R438.1
unnamed: R176.1, R323.1, R415.2
unnamed: R176.2, R178.2, R323.2, R416.1
unnamed: R177.1, R346.1, R438.2
unnamed: R177.2, R179.2, R346.2, R439.1
unnamed: R180.1, R324.1, R416.2
unnamed: R180.2, R182.2, R324.2, R417.1
unnamed: R181.1, R347.1, R439.2
unnamed: R181.2, R183.2, R347.2, R440.1
unnamed: R184.1, R325.1, R417.2
unnamed: R184.2, R186.2, R325.2, R418.1
unnamed: R185.1, R348.1, R440.2
unnamed: R185.2, R187.2, R348.2, R441.1
unnamed: R188.1, R326.1, R418.2
unnamed: R188.2, R190.2, R326.2, R419.1
unnamed: R189.1, R349.1, R441.2
unnamed: R189.2, R191.2, R349.2, R442.1
unnamed: R192.1, R327.1, R419.2
unnamed: R192.2, R194.2, R327.2, R420.1
unnamed: R193.1, R350.1, R442.2
unnamed: R193.2, R195.2, R350.2, R443.1
unnamed: R196.1, R328.1, R420.2
unnamed: R196.2, R198.2, R328.2, R421.1
unnamed: R197.1, R351.1, R443.2
unnamed: R197.2, R199.2, R351.2, R444.1
unnamed: R200.1, R329.1, R421.2
unnamed: R200.2, R202.2, R329.2, R422.1
unnamed: R201.1, R352.1, R444.2
unnamed: R201.2, R203.2, R352.2, R445.1
unnamed: R204.1, R330.1, R422.2
unnamed: R204.2, R206.2, R330.2, R423.1
unnamed: R205.1, R353.1, R445.2
unnamed: R205.2, R207.2, R353.2, R446.1
unnamed: R208.1, R331.1, R423.2
unnamed: R208.2, R210.2, R331.2, R424.1
unnamed: R209.1, R354.1, R446.2
unnamed: R209.2, R211.2, R354.2, R447.1
unnamed: R212.1, R332.1, R424.2
unnamed: R212.2, R214.2, R332.2, R425.1
unnamed: R213.1, R355.1, R447.2
unnamed: R213.2, R215.2, R355.2, R448.1
unnamed: R216.1, R333.1, R425.2
unnamed: R216.2, R218.2, R333.2, R426.1
unnamed: R217.1, R356.1, R448.2
unnamed: R217.2, R219.2, R356.2, R449.1
unnamed: R220.1, R334.1, R426.2
unnamed: R220.2, R222.2, R334.2, R427.1
unnamed: R221.1, R357.1, R449.2
unnamed: R221.2, R223.2, R357.2, R450.1
unnamed: R224.1, R335.1, R427.2
unnamed: R224.2, R226.2, R335.2, R428.1
unnamed: R225.1, R358.1, R450.2
unnamed: R225.2, R227.2, R358.2, R451.1
unnamed: R228.1, R336.1, R428.2
unnamed: R228.2, R230.2, R336.2, R429.1
unnamed: R229.1, R359.1, R451.2
unnamed: R229.2, R231.2, R359.2, R452.1
unnamed: R232.1, R337.1, R429.2
unnamed: R232.2, R234.2, R337.2, R430.1
unnamed: R233.1, R360.1, R452.2
unnamed: R233.2, R235.2, R360.2, R453.1
unnamed: R236.1, R338.1, R430.2
unnamed: R236.2, R238.2, R338.2, R431.1
unnamed: R237.1, R361.1, R453.2
unnamed: R237.2, R239.2, R361.2, R454.1
unnamed: R240.1, R339.1, R431.2
unnamed: R240.2, R242.2, R339.2, R432.1
unnamed: R241.1, R362.1, R454.2
unnamed: R241.2, R243.2, R362.2, R455.1
unnamed: R244.1, R340.1, R432.2
unnamed: R244.2, R246.2, R340.2, R433.1
unnamed: R245.1, R363.1, R455.2
unnamed: R245.2, R247.2, R363.2, R456.1
unnamed: R248.1, R341.1, R433.2
unnamed: R248.2, R250.2, R341.2, R434.1
unnamed: R249.1, R364.1, R456.2
unnamed: R249.2, R251.2, R364.2, R457.1
unnamed: R252.1, R342.1, R434.2
unnamed: R252.2, R254.2, R342.2, R435.1
unnamed: R253.1, R365.1, R457.2
unnamed: R253.2, R255.2, R365.2, R458.1
unnamed: R256.1, R343.1, R435.2
unnamed: R257.1, R366.1, R458.2
unnamed: R258.1, R266.2
unnamed: R260.1, R267.2
unnamed: R266.1, RV3.2, RV3.3
unnamed: R267.1, RV4.2, RV4.3
unnamed: R9.1, R275.1, R367.2
unnamed: R30.1, R289.1, R381.2
unnamed: R30.2, R31.2, R289.2, R382.1
unnamed: R32.1, R290.1, R382.2
unnamed: R32.2, R33.2, R290.2, R383.1
unnamed: R34.1, R291.1, R383.2
unnamed: R34.2, R35.2, R291.2, R384.1
unnamed: R36.1, R292.1, R384.2
unnamed: R36.2, R37.2, R292.2, R385.1
unnamed: R38.1, R293.1, R385.2
unnamed: R38.2, R39.2, R293.2, R386.1
unnamed: R40.1, R294.1, R386.2
unnamed: R40.2, R41.2, R294.2, R387.1
unnamed: R42.1, R295.1, R387.2
unnamed: R42.2, R43.2, R295.2, R388.1
unnamed: R44.1, R296.1, R388.2
unnamed: R44.2, R45.2, R296.2, R389.1
unnamed: R46.1, R297.1, R389.2
unnamed: RN1.8 (R1.2), U20.C17 (IO_L20N_T3_A19_15)
unnamed: RN1.7 (R2.2), U20.B18 (IO_L10P_T1_AD11P_15)
unnamed: RN1.6 (R3.2), U20.B17 (IO_L7N_T1_AD2N_15)
unnamed: RN1.5 (R4.2), U20.A18 (IO_L10N_T1_AD11N_15)
unnamed: RN2.8 (R1.2), U20.E18 (IO_L21P_T3_DQS_15)
unnamed: RN2.7 (R2.2), U20.E17 (IO_L16P_T2_A28_15)
unnamed: RN2.6 (R3.2), U20.D18 (IO_L21N_T3_DQS_A18_15)
unnamed: RN2.5 (R4.2), U20.D17 (IO_L16N_T2_A27_15)
unnamed: RN3.7 (R2.2), U20.G18 (IO_L22P_T3_A17_15)
unnamed: RN3.6 (R3.2), U20.G17 (IO_L18N_T2_A23_15)
unnamed: RN3.5 (R4.2), U20.F18 (IO_L22N_T3_A16_15)
unnamed: R466.2, RN4.7 (R2.2), U1.26 (SDOUT)
unnamed: RN4.6 (R3.2), U1.27 (OSCLK)
unnamed: RN4.5 (R4.2), U1.28 (OLRCK)
unnamed: C199.2, R459.1, U1.8 (FILT)
unnamed: C200.1, U1.5 (RXN)
unnamed: C201.1, U1.3 (RXP1)
unnamed: C202.1, U1.2 (RXP2)
unnamed: C203.1, FB1.2, U1.6 (VA)
unnamed: U2.15 (QA), U3.17 (B2), U3.18 (B1)
unnamed: U2.1 (QB), U3.15 (B4), U3.16 (B3)
unnamed: U2.2 (QC), U3.13 (B6), U3.14 (B5)
unnamed: U2.3 (QD), U3.11 (B8), U3.12 (B7)
unnamed: U2.4 (QE), U4.17 (B2), U4.18 (B1)
unnamed: U2.5 (QF), U4.15 (B4), U4.16 (B3)
unnamed: U2.6 (QG), U4.13 (B6), U4.14 (B5)
unnamed: U2.9 (QH'), U6.14 (SER)
unnamed: U2.7 (QH), U4.11 (B8), U4.12 (B7)
unnamed: R1.1, U3.2 (A1), U3.3 (A2)
unnamed: R2.1, U3.4 (A3), U3.5 (A4)
unnamed: R3.1, U3.6 (A5), U3.7 (A6)
unnamed: R4.1, U3.8 (A7), U3.9 (A8)
unnamed: R5.1, U4.2 (A1), U4.3 (A2)
unnamed: R6.1, U4.4 (A3), U4.5 (A4)
unnamed: R7.1, U4.6 (A5), U4.7 (A6)
unnamed: R8.1, U4.8 (A7), U4.9 (A8)
unnamed: R16.1, U5.2 (A1), U5.3 (A2)
unnamed: R19.1, U5.4 (A3), U5.5 (A4)
unnamed: R21.1, U5.6 (A5), U5.7 (A6)
unnamed: R23.1, U5.8 (A7), U5.9 (A8)
unnamed: U5.17 (B2), U5.18 (B1), U6.15 (QA)
unnamed: U5.15 (B4), U5.16 (B3), U6.1 (QB)
unnamed: U5.13 (B6), U5.14 (B5), U6.2 (QC)
unnamed: U5.11 (B8), U5.12 (B7), U6.3 (QD)
unnamed: U6.4 (QE), U7.17 (B2), U7.18 (B1)
unnamed: U6.5 (QF), U7.15 (B4), U7.16 (B3)
unnamed: U6.6 (QG), U7.13 (B6), U7.14 (B5)
unnamed: U6.9 (QH'), U9.14 (SER)
unnamed: U6.7 (QH), U7.11 (B8), U7.12 (B7)
unnamed: R25.1, U7.2 (A1), U7.3 (A2)
unnamed: R27.1, U7.4 (A3), U7.5 (A4)
unnamed: R29.1, U7.6 (A5), U7.7 (A6)
unnamed: R31.1, U7.8 (A7), U7.9 (A8)
unnamed: R33.1, U8.2 (A1), U8.3 (A2)
unnamed: R35.1, U8.4 (A3), U8.5 (A4)
unnamed: R37.1, U8.6 (A5), U8.7 (A6)
unnamed: R39.1, U8.8 (A7), U8.9 (A8)
unnamed: U8.17 (B2), U8.18 (B1), U9.15 (QA)
unnamed: U8.15 (B4), U8.16 (B3), U9.1 (QB)
unnamed: U8.13 (B6), U8.14 (B5), U9.2 (QC)
unnamed: U8.11 (B8), U8.12 (B7), U9.3 (QD)
unnamed: R41.1, U10.2 (A1), U10.3 (A2)
unnamed: R43.1, U10.4 (A3), U10.5 (A4)
unnamed: R45.1, U10.6 (A5), U10.7 (A6)
unnamed: RV1.1, U10.8 (A7), U10.9 (A8)
unnamed: U9.4 (QE), U10.17 (B2), U10.18 (B1)
unnamed: U9.5 (QF), U10.15 (B4), U10.16 (B3)
unnamed: U9.6 (QG), U10.13 (B6), U10.14 (B5)
unnamed: U10.11 (B8), U10.12 (B7), U11.4 (Y)
unnamed: U9.7 (QH), U11.2 (A)
unnamed: C66.1, R99.2, U12.7 (SET)
unnamed: C197.2, U13.43 (IN0)
unnamed: C196.1, U13.44 (IN0b)
unnamed: U13.4 (X1), Y1.2
unnamed: U13.7 (X2), Y1.4
unnamed: U13.5 (XA), Y1.3
unnamed: U13.6 (XB), Y1.1
unnamed: R69.1, U13.31 (~LOS1)
unnamed: R70.1, U13.36 (~LOS3)
unnamed: R76.2, U14.24 (RBIAS)
unnamed: R90.1, U14.22 (VBUS)
unnamed: C12.1, R54.2, U15.59 (XTALN), X1.2 (-)
unnamed: C13.1, R54.1, U15.58 (XTALP), X1.1 (+)
unnamed: C54.1, R97.1, U19.3 (CT)
unnamed: R96.1, U19.7 (HO)
unnamed: R95.1, U19.5 (LO)
unnamed: R97.2, U19.2 (RT)
unnamed: R262.1, U20.J18 (IO_L23N_T3_FWE_B_15)
unnamed: R261.1, U20.J17 (IO_L23P_T3_FOE_B_15)
unnamed: R63.1, U20.T5 (IO_L12P_T1_MRCC_34)
unnamed: R65.1, U20.N5 (IO_L13P_T2_MRCC_34)
unnamed: D22.1, R270.2, U20.P10 (DONE_0)
unnamed: R264.1, U20.P7 (INIT_B_0)
unnamed: R59.2, R93.1, U21.5 (FB)
unnamed: C242.1, U21.9 (SS/TR)
unnamed: C25.2, L4.1, U24.2 (SW)
unnamed: C25.1, U24.6 (VBST)
unnamed: R79.2, R80.1, U24.4 (VFB)
unnamed: C67.1, R94.2, U25.7 (SET)
unnamed: C32.2, L6.1, U26.2 (SW)
unnamed: C32.1, U26.6 (VBST)
unnamed: R61.2, R62.1, U26.4 (VFB)
unnamed: R109.1, R110.2, U27.2 (A)
unnamed: R109.2, U27.4 (Y), U28.2 (A)
unnamed: R111.1, U29.2 (A1), U29.3 (A2)
unnamed: R114.1, U29.4 (A3), U29.5 (A4)
unnamed: R116.1, U29.6 (A5), U29.7 (A6)
unnamed: R118.1, U29.8 (A7), U29.9 (A8)
unnamed: U29.17 (B2), U29.18 (B1), U30.15 (QA)
unnamed: U29.15 (B4), U29.16 (B3), U30.1 (QB)
unnamed: U29.13 (B6), U29.14 (B5), U30.2 (QC)
unnamed: U29.11 (B8), U29.12 (B7), U30.3 (QD)
unnamed: U30.4 (QE), U31.17 (B2), U31.18 (B1)
unnamed: U30.5 (QF), U31.15 (B4), U31.16 (B3)
unnamed: U30.6 (QG), U31.13 (B6), U31.14 (B5)
unnamed: U30.9 (QH'), U33.14 (SER)
unnamed: U30.7 (QH), U31.11 (B8), U31.12 (B7)
unnamed: U30.14 (SER), U39.4 (Y)
unnamed: R120.1, U31.2 (A1), U31.3 (A2)
unnamed: R122.1, U31.4 (A3), U31.5 (A4)
unnamed: R124.1, U31.6 (A5), U31.7 (A6)
unnamed: R126.1, U31.8 (A7), U31.9 (A8)
unnamed: R128.1, U32.2 (A1), U32.3 (A2)
unnamed: R130.1, U32.4 (A3), U32.5 (A4)
unnamed: R132.1, U32.6 (A5), U32.7 (A6)
unnamed: R134.1, U32.8 (A7), U32.9 (A8)
unnamed: U32.17 (B2), U32.18 (B1), U33.15 (QA)
unnamed: U32.15 (B4), U32.16 (B3), U33.1 (QB)
unnamed: U32.13 (B6), U32.14 (B5), U33.2 (QC)
unnamed: U32.11 (B8), U32.12 (B7), U33.3 (QD)
unnamed: U33.4 (QE), U34.17 (B2), U34.18 (B1)
unnamed: U33.5 (QF), U34.15 (B4), U34.16 (B3)
unnamed: U33.6 (QG), U34.13 (B6), U34.14 (B5)
unnamed: U33.9 (QH'), U36.14 (SER)
unnamed: U33.7 (QH), U34.11 (B8), U34.12 (B7)
unnamed: R136.1, U34.2 (A1), U34.3 (A2)
unnamed: R138.1, U34.4 (A3), U34.5 (A4)
unnamed: R140.1, U34.6 (A5), U34.7 (A6)
unnamed: R142.1, U34.8 (A7), U34.9 (A8)
unnamed: R144.1, U35.2 (A1), U35.3 (A2)
unnamed: R146.1, U35.4 (A3), U35.5 (A4)
unnamed: R148.1, U35.6 (A5), U35.7 (A6)
unnamed: R150.1, U35.8 (A7), U35.9 (A8)
unnamed: U35.17 (B2), U35.18 (B1), U36.15 (QA)
unnamed: U35.15 (B4), U35.16 (B3), U36.1 (QB)
unnamed: U35.13 (B6), U35.14 (B5), U36.2 (QC)
unnamed: U35.11 (B8), U35.12 (B7), U36.3 (QD)
unnamed: U36.4 (QE), U37.17 (B2), U37.18 (B1)
unnamed: U36.5 (QF), U37.15 (B4), U37.16 (B3)
unnamed: U36.6 (QG), U37.13 (B6), U37.14 (B5)
unnamed: U36.7 (QH), U38.2 (A)
unnamed: R152.1, U37.2 (A1), U37.3 (A2)
unnamed: R154.1, U37.4 (A3), U37.5 (A4)
unnamed: R156.1, U37.6 (A5), U37.7 (A6)
unnamed: RV2.1, U37.8 (A7), U37.9 (A8)
unnamed: U37.11 (B8), U37.12 (B7), U38.4 (Y)
unnamed: U40.4 (Y), U44.14 (SER)
unnamed: R164.1, U41.2 (A1), U41.3 (A2)
unnamed: R170.1, U41.4 (A3), U41.5 (A4)
unnamed: R174.1, U41.6 (A5), U41.7 (A6)
unnamed: R178.1, U41.8 (A7), U41.9 (A8)
unnamed: U41.17 (B2), U41.18 (B1), U43.15 (QA)
unnamed: U41.15 (B4), U41.16 (B3), U43.1 (QB)
unnamed: U41.13 (B6), U41.14 (B5), U43.2 (QC)
unnamed: U41.11 (B8), U41.12 (B7), U43.3 (QD)
unnamed: R166.1, U42.2 (A1), U42.3 (A2)
unnamed: R171.1, U42.4 (A3), U42.5 (A4)
unnamed: R175.1, U42.6 (A5), U42.7 (A6)
unnamed: R179.1, U42.8 (A7), U42.9 (A8)
unnamed: U42.17 (B2), U42.18 (B1), U44.15 (QA)
unnamed: U42.15 (B4), U42.16 (B3), U44.1 (QB)
unnamed: U42.13 (B6), U42.14 (B5), U44.2 (QC)
unnamed: U42.11 (B8), U42.12 (B7), U44.3 (QD)
unnamed: U43.4 (QE), U45.17 (B2), U45.18 (B1)
unnamed: U43.5 (QF), U45.15 (B4), U45.16 (B3)
unnamed: U43.6 (QG), U45.13 (B6), U45.14 (B5)
unnamed: U43.9 (QH'), U49.14 (SER)
unnamed: U43.7 (QH), U45.11 (B8), U45.12 (B7)
unnamed: U44.4 (QE), U46.17 (B2), U46.18 (B1)
unnamed: U44.5 (QF), U46.15 (B4), U46.16 (B3)
unnamed: U44.6 (QG), U46.13 (B6), U46.14 (B5)
unnamed: U44.9 (QH'), U50.14 (SER)
unnamed: U44.7 (QH), U46.11 (B8), U46.12 (B7)
unnamed: R182.1, U45.2 (A1), U45.3 (A2)
unnamed: R186.1, U45.4 (A3), U45.5 (A4)
unnamed: R190.1, U45.6 (A5), U45.7 (A6)
unnamed: R194.1, U45.8 (A7), U45.9 (A8)
unnamed: R183.1, U46.2 (A1), U46.3 (A2)
unnamed: R187.1, U46.4 (A3), U46.5 (A4)
unnamed: R191.1, U46.6 (A5), U46.7 (A6)
unnamed: R195.1, U46.8 (A7), U46.9 (A8)
unnamed: R198.1, U47.2 (A1), U47.3 (A2)
unnamed: R202.1, U47.4 (A3), U47.5 (A4)
unnamed: R206.1, U47.6 (A5), U47.7 (A6)
unnamed: R210.1, U47.8 (A7), U47.9 (A8)
unnamed: U47.17 (B2), U47.18 (B1), U49.15 (QA)
unnamed: U47.15 (B4), U47.16 (B3), U49.1 (QB)
unnamed: U47.13 (B6), U47.14 (B5), U49.2 (QC)
unnamed: U47.11 (B8), U47.12 (B7), U49.3 (QD)
unnamed: R199.1, U48.2 (A1), U48.3 (A2)
unnamed: R203.1, U48.4 (A3), U48.5 (A4)
unnamed: R207.1, U48.6 (A5), U48.7 (A6)
unnamed: R211.1, U48.8 (A7), U48.9 (A8)
unnamed: U48.17 (B2), U48.18 (B1), U50.15 (QA)
unnamed: U48.15 (B4), U48.16 (B3), U50.1 (QB)
unnamed: U48.13 (B6), U48.14 (B5), U50.2 (QC)
unnamed: U48.11 (B8), U48.12 (B7), U50.3 (QD)
unnamed: U49.4 (QE), U51.17 (B2), U51.18 (B1)
unnamed: U49.5 (QF), U51.15 (B4), U51.16 (B3)
unnamed: U49.6 (QG), U51.13 (B6), U51.14 (B5)
unnamed: U49.9 (QH'), U55.14 (SER)
unnamed: U49.7 (QH), U51.11 (B8), U51.12 (B7)
unnamed: U50.4 (QE), U52.17 (B2), U52.18 (B1)
unnamed: U50.5 (QF), U52.15 (B4), U52.16 (B3)
unnamed: U50.6 (QG), U52.13 (B6), U52.14 (B5)
unnamed: U50.9 (QH'), U56.14 (SER)
unnamed: U50.7 (QH), U52.11 (B8), U52.12 (B7)
unnamed: R214.1, U51.2 (A1), U51.3 (A2)
unnamed: R218.1, U51.4 (A3), U51.5 (A4)
unnamed: R222.1, U51.6 (A5), U51.7 (A6)
unnamed: R226.1, U51.8 (A7), U51.9 (A8)
unnamed: R215.1, U52.2 (A1), U52.3 (A2)
unnamed: R219.1, U52.4 (A3), U52.5 (A4)
unnamed: R223.1, U52.6 (A5), U52.7 (A6)
unnamed: R227.1, U52.8 (A7), U52.9 (A8)
unnamed: R230.1, U53.2 (A1), U53.3 (A2)
unnamed: R234.1, U53.4 (A3), U53.5 (A4)
unnamed: R238.1, U53.6 (A5), U53.7 (A6)
unnamed: R242.1, U53.8 (A7), U53.9 (A8)
unnamed: U53.17 (B2), U53.18 (B1), U55.15 (QA)
unnamed: U53.15 (B4), U53.16 (B3), U55.1 (QB)
unnamed: U53.13 (B6), U53.14 (B5), U55.2 (QC)
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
